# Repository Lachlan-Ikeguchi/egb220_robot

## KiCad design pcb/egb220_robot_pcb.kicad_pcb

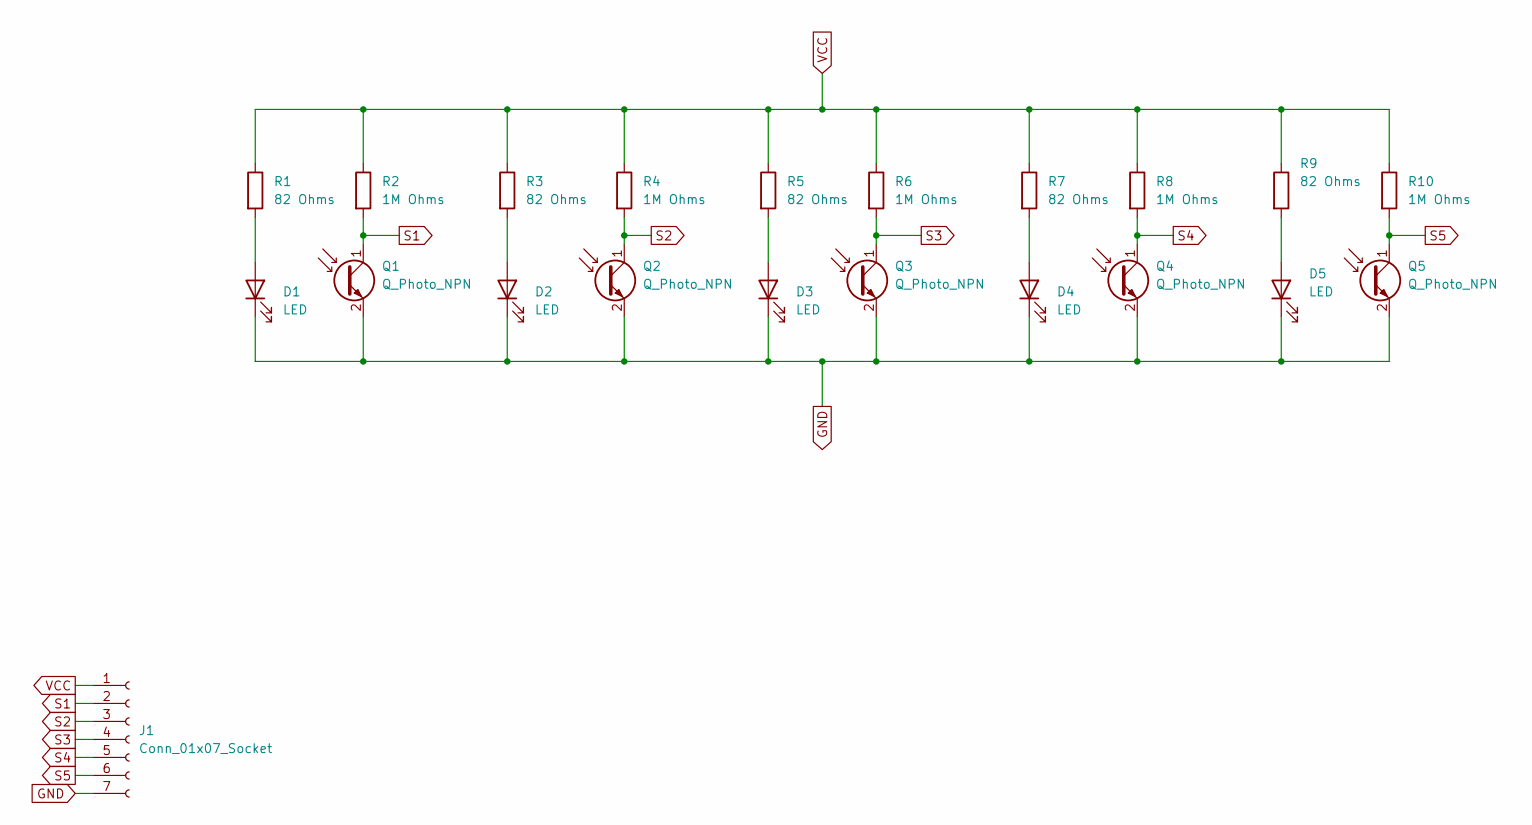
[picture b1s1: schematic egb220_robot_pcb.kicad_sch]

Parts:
D1, D2, D3, D4, D5: LED; LED_D3.0mm_IRGrey
J1: Conn_01x07_Socket; PinSocket_2x04_P2.54mm_Vertical
Q1, Q2, Q3, Q4, Q5: Q_Photo_NPN; LED_D3.0mm_IRBlack
R1, R3, R5, R7, R9: 82 Ohms; R_0603_1608Metric_Pad0.98x0.95mm_HandSolder
R2, R4, R6, R8, R10: 1M Ohms; R_0603_1608Metric_Pad0.98x0.95mm_HandSolder

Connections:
GND: D1.1 (K), D2.1 (K), D3.1 (K), D4.1 (K), D5.1 (K), J1.7, Q1.2 (E), Q2.2 (E), Q3.2 (E), Q4.2 (E), Q5.2 (E)
unnamed: D1.2 (A), R1.2
unnamed: D2.2 (A), R3.2
unnamed: D3.2 (A), R5.2
unnamed: D4.2 (A), R7.2
unnamed: D5.2 (A), R9.2
S1: J1.2, Q1.1 (C), R2.2
S2: J1.3, Q2.1 (C), R4.2
S3: J1.4, Q3.1 (C), R6.2
S4: J1.5, Q4.1 (C), R8.2
S5: J1.6, Q5.1 (C), R10.2
VCC: J1.1, R1.1, R2.1, R3.1, R4.1, R5.1, R6.1, R7.1, R8.1, R9.1, R10.1

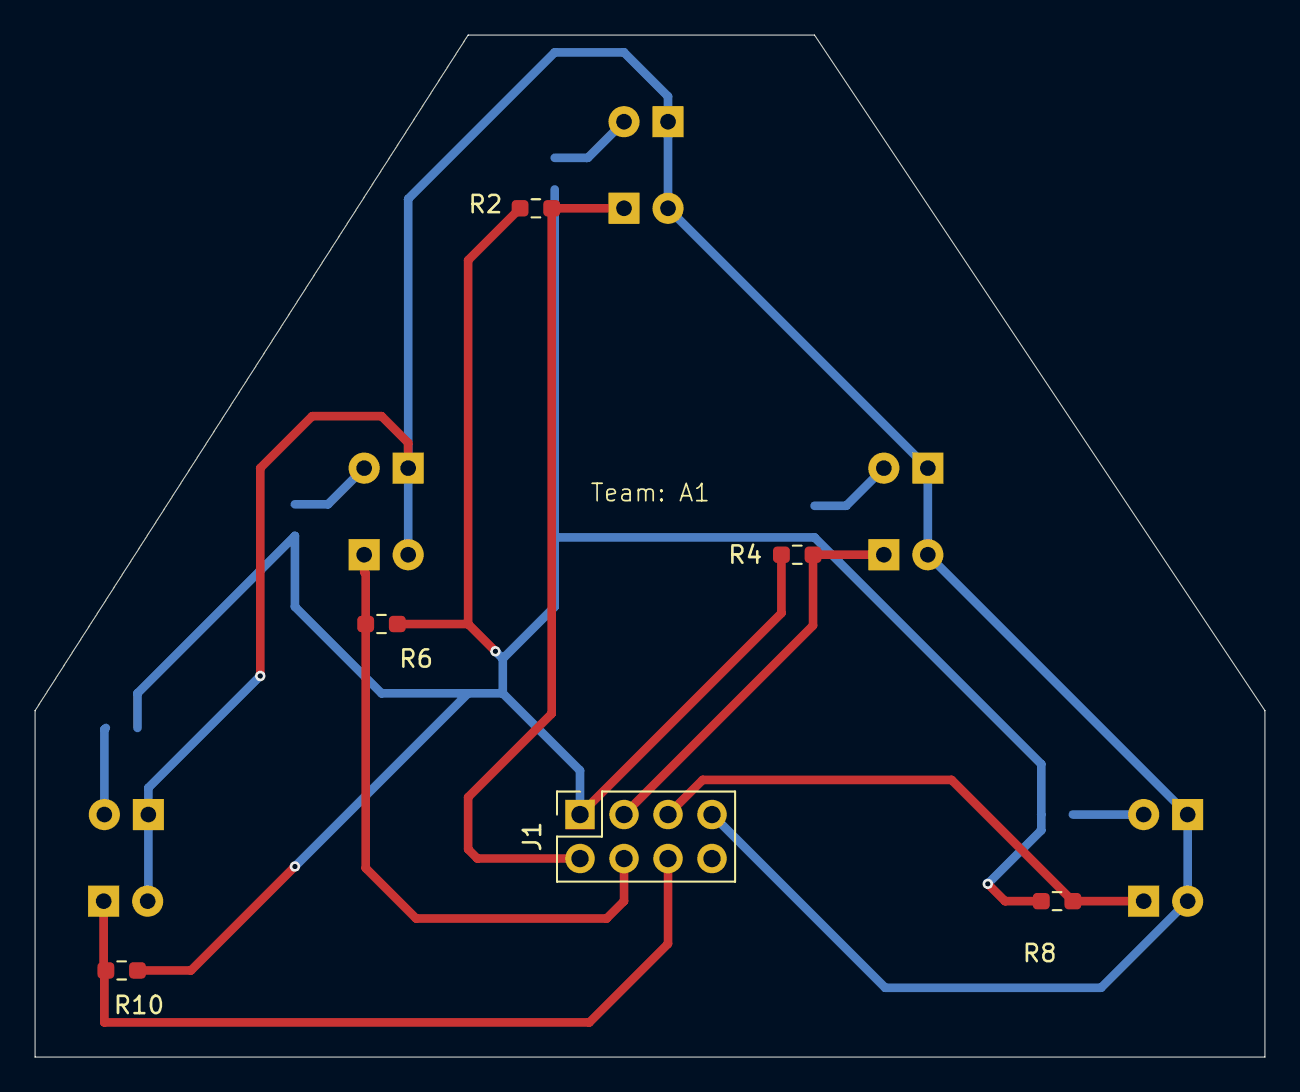
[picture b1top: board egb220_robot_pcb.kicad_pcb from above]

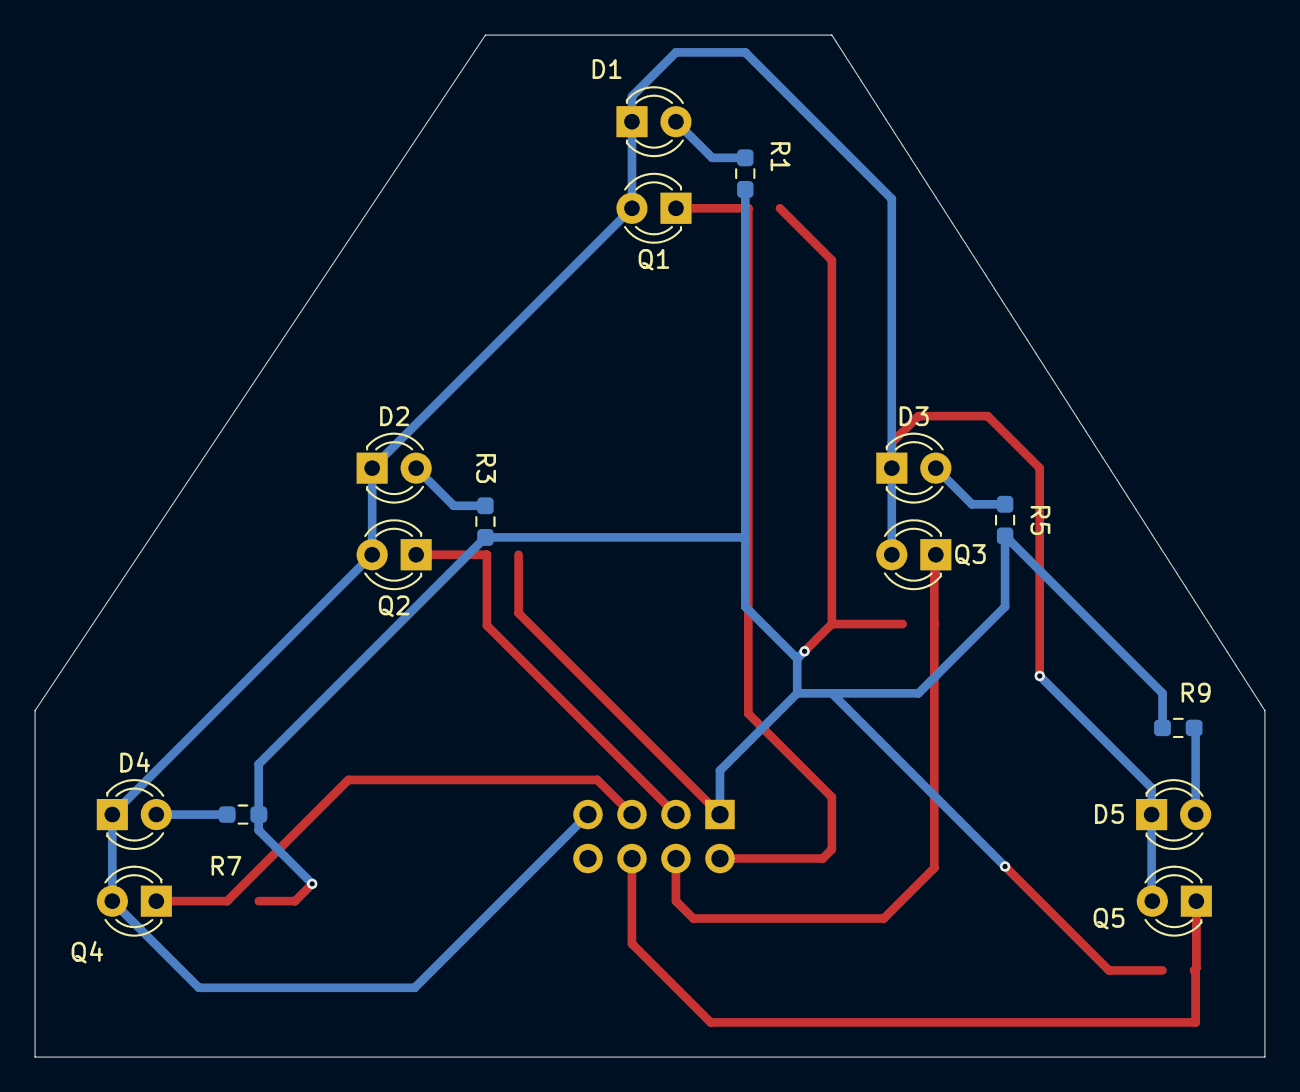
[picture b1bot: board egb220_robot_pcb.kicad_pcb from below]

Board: 2 copper layers, 71.0 x 59.0 mm, 21 parts (15 on the bottom side), 12 nets.

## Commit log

2026-03-07 feat(libraries): added libraries
2026-03-07 refactor(libraries): deleted local libraries in favour of system
2026-03-08 docs(README): added readme
2026-03-09 docs(readme): added coding requirements based on NASA's JPL
2026-03-10 feat(PCB): Completed sensor array and first submission
